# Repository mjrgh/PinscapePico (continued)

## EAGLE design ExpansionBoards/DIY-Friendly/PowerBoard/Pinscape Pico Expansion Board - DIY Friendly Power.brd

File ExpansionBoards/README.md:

# Pinscape Pico Expansion Boards

This folder has EAGLE plans for several circuit board designs that go with
the Pinscape Pico software.  These plans are all open-source designs that
anyone is free to build.

* <b>DIY-Friendly:</b> A comprehensive I/O controller for a virtual pinball
cabinet, with enough button ports and feedback device ports to connect just
about everything in a high-end build.  It uses entirely through-hole parts
that are easy to solder by hand, which is what makes it DIY-friendly.  The
project consists of two boards that are meant to be built and deployed as
a set (since I couldn't fit everything onto a single board, given the amount
of space that the through-hole parts take up).

* <b>Pro:</b> Another comprehensive expansion board, with essentially the
same functionality as the DIY-Friendly board set, but this time using mostly
surface-mount (SMD) parts.  The SMD parts are much smaller than the through-hole
parts used on the DIY board, allowing everything to be packed into a single
board.  The tradeoff is that a lot of the SMD parts used in the design are
difficult to solder by hand, precisely because they're so small.  So this
board is really meant to be assembled by factory equipment.  That's why I
refer to it as the "Pro" board - it's probably only going to be cost-effective
to build if you're going to build at least 50 or 100 units, and if you're
making that many, it's probably because you plan to sell them at a profit.
The designs are open-source, so you're free to do that if you have a retail
shop set up and you're willing to back your sales with warranty and technical
support (since, as they're open source, the designs themselves don't come
with any warranty).

* <b>IR-RX:</b> A small satellite board for the DIY-Friendly or Pro boards
that holds an IR receiver chip, and connects back to the expansion board
with a ribbon cable.  This lets you position an IR receiver anywhere
inside or outside your cabinet, so that it can be in line-of-sight to the
remote controls you want to point at it.

* <b>KL25Z Adapter:</b> This is for people with an existing set of the
original Pinscape KL25Z expansion boards.  The board plugs into the KL25Z
expansion boards where the KL25Z would normally go, letting a Pico take the
place of the KL25Z.  This lets you use your existing expansion boards with
the new Pinscape Pico software, and without having to re-wire your cabinet
for a new expansion board set.  (It doesn't act as a true general-purpose
KL25Z emulator, though, since it's very specifically wired for the original
Pinscape boards.)

* <b>Power Distribution:</b> A simple board designed to help tidy up your
virtual pin cab power supply wiring.  It doesn't do much other than route
power from one connector to another, but the idea is that it makes your
wiring simpler and more structured.  It does have a few active features: it
has a 6.3V regulator for powering #555 lamps (the type commonly used in
arcade pushbuttons); it provides main power switching (through a relay) for
all of the secondary supplies, based on the main PC power on/off status; and
it includes wiring for a coin door safety interlock switch for a
high-voltage (48V) supply, so that the high-voltage power is automatically
cut off whenever you open the coin door to do maintenance work inside the
cabinet.  It also features connectors that match the power connectors on the
DIY-Friendly and Pro expansion boards, again just to make the wiring tidier.
<p>
This board can be used with any I/O controller, not just Pinscape
Pico.  It does include two connectors designed especially to match
the layout of the Pinscape Pico expansion board power inputs, but
other controllers are likely to have similar power input requirements,
so it should be easy to adapt in most cases.
</p>

* <b>Flasher Panel:</b> A board designed to sit behind an RGB LED flasher
panel in a standard-width pin cab, to provide all of the electronics and
wiring to the flashers, including the five high-current (350mA) RGB LEDs.
It uses a 16-wire ribbon cable connector that matches the layout of the
Flasher port on the Pinscape Pico and KL25Z expansion boards, to make the
wiring between the controller and panel very easy and neat.  Like the Power
Distribution board, this one is designed to replace ad hoc wiring to make
your build a little tidier, and it can be used with any I/O controller.

## How to fabricate the boards

See [Fabricating the Expansion Boards](http://mjrnet.org/pinscape/BuildGuideV2/BuildGuide.php?sid=expanFab)
in the [Pinscape Build Guide](http://mjrnet.org/pinscape/BuildGuideV2/BuildGuide.php).
That explains the process in terms of the original KL25Z Pinscape boards, but
it applies equally well to the Pinscape Pico boards - just substitute the EAGLE
files from this repository.

## Bills of Materials (BOMs)

Each circuit board has an accompanying BOM file, in .csv (Comma-Separated
Value) format.  To view these, open them in a spreadsheet program like
Microsoft Excel, Apple Numbers, or Google Sheets.

The reason these are in CSV format rather than plain text is that Mouser and
Digikey will accept them as uploads, to construct a shopping cart without a
lot of manual data entry.  But you should carefully review the results.  For
one thing, the sites aren't always perfect at matching the BOM line items to
their inventory, so check that everything looks plausibly correct before
ordering.  For another, items go out of stock.  Some items might even be out
of production by the time you order, especially if the BOM you're working
from is more than five minutes old, since the manufacturers constantly
change their product lineups.  For out-of-stock or obsolete items, you'll
have to select suitable substitutes.  For generic parts like resistors and
capacitors, substitutes should always be easy to find - just match the Ohms
or "uF" values, and the physical package type and size.  For more complex
parts, such as transistors and IC chips, it can be more difficult to select
substitutes; ask on the forums if you're in doubt, and hopefully someone
with an electronics background can point you in the right direction.

## Copyright and license

The expansion board material is released under the same copyright and
license terms as the rest of the Pinscape Pico project.  Copyright 2025
Michael J Roberts; released under a BSD 3-clause license with NO WARRANTY.

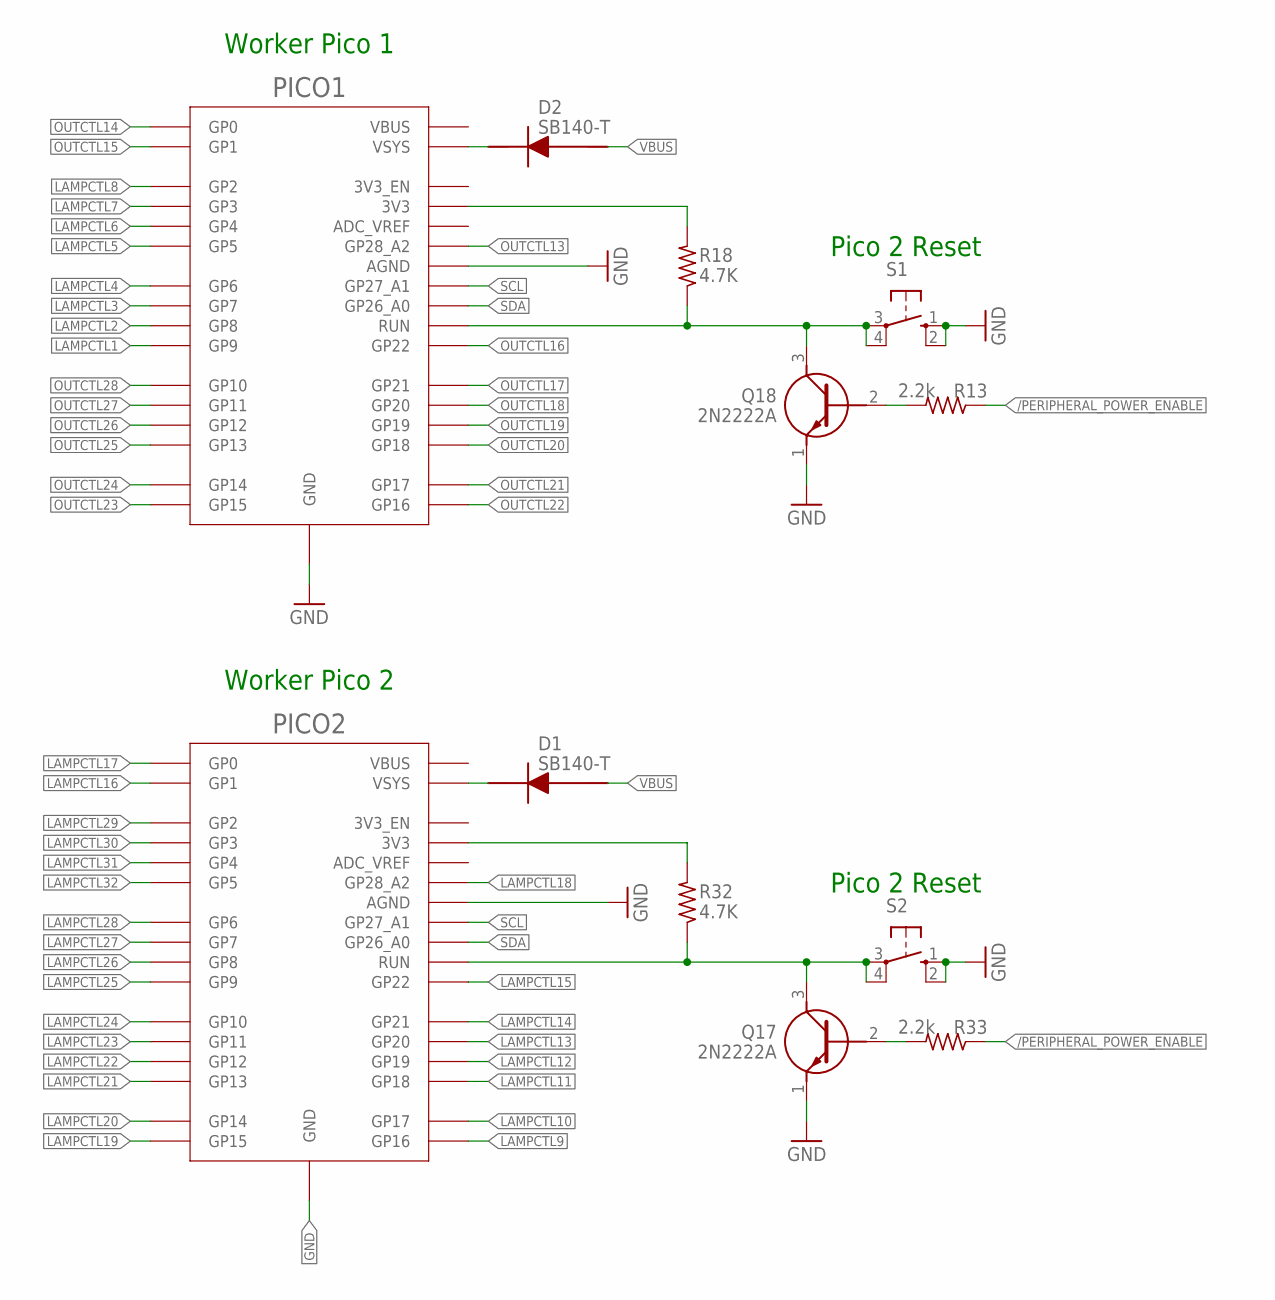
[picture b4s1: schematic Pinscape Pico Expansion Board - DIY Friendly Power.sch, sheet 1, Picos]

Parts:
D1, D2: SB140-T; DIOAD1408W86L464D236
PICO1, PICO2: RPI_PICO_NO_DEBUG; RPI_PICO_TH_NO_DEBUG
Q17, Q18: 2N2222A
R13, R33: 2.2k; 0204/7; PARTNO 660-MFS1/4DCT52R47R0
R18, R32: 4.7K; 0204/7; PARTNO 660-MFS1/4DCT52R47R0
S1, S2: 10-XX; B3F-10XX

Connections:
/PERIPHERAL_POWER_ENABLE: R13.1, R33.1; also elsewhere on the board
GND: PICO1.AGND, PICO1.GND@1 (GND), PICO1.GND@2 (GND), PICO1.GND@3 (GND), PICO1.GND@4 (GND), PICO1.GND@6 (GND), PICO1.GND@7 (GND), PICO1.GND@8 (GND), PICO2.AGND, PICO2.GND@1 (GND), PICO2.GND@2 (GND), PICO2.GND@3 (GND), PICO2.GND@4 (GND), PICO2.GND@6 (GND), PICO2.GND@7 (GND), PICO2.GND@8 (GND), Q17.1 (E), Q18.1 (E), S1.1 (S), S1.2 (S1), S2.1 (S), S2.2 (S1); also elsewhere on the board
LAMPCTL1: PICO1.GP9; also elsewhere on the board
LAMPCTL2: PICO1.GP8; also elsewhere on the board
LAMPCTL3: PICO1.GP7; also elsewhere on the board
LAMPCTL4: PICO1.GP6; also elsewhere on the board
LAMPCTL5: PICO1.GP5; also elsewhere on the board
LAMPCTL6: PICO1.GP4; also elsewhere on the board
LAMPCTL7: PICO1.GP3; also elsewhere on the board
LAMPCTL8: PICO1.GP2; also elsewhere on the board
LAMPCTL9: PICO2.GP16; also elsewhere on the board
LAMPCTL10: PICO2.GP17; also elsewhere on the board
LAMPCTL11: PICO2.GP18; also elsewhere on the board
LAMPCTL12: PICO2.GP19; also elsewhere on the board
LAMPCTL13: PICO2.GP20; also elsewhere on the board
LAMPCTL14: PICO2.GP21; also elsewhere on the board
LAMPCTL15: PICO2.GP22; also elsewhere on the board
LAMPCTL16: PICO2.GP1; also elsewhere on the board
LAMPCTL17: PICO2.GP0; also elsewhere on the board
LAMPCTL18: PICO2.GP28_A2; also elsewhere on the board
LAMPCTL19: PICO2.GP15; also elsewhere on the board
LAMPCTL20: PICO2.GP14; also elsewhere on the board
LAMPCTL21: PICO2.GP13; also elsewhere on the board
LAMPCTL22: PICO2.GP12; also elsewhere on the board
LAMPCTL23: PICO2.GP11; also elsewhere on the board
LAMPCTL24: PICO2.GP10; also elsewhere on the board
LAMPCTL25: PICO2.GP9; also elsewhere on the board
LAMPCTL26: PICO2.GP8; also elsewhere on the board
LAMPCTL27: PICO2.GP7; also elsewhere on the board
LAMPCTL28: PICO2.GP6; also elsewhere on the board
LAMPCTL29: PICO2.GP2; also elsewhere on the board
LAMPCTL30: PICO2.GP3; also elsewhere on the board
LAMPCTL31: PICO2.GP4; also elsewhere on the board
LAMPCTL32: PICO2.GP5; also elsewhere on the board
unnamed: D1.1 (K), PICO2.VSYS
unnamed: D2.1 (K), PICO1.VSYS
unnamed: PICO2.3V3, R32.2
unnamed: Q17.2 (B), R33.2
unnamed: PICO2.RUN, Q17.3 (C), R32.1, S2.3, S2.4 (P1)
unnamed: PICO1.3V3, R18.2
unnamed: Q18.2 (B), R13.2
unnamed: PICO1.RUN, Q18.3 (C), R18.1, S1.3, S1.4 (P1)
OUTCTL13: PICO1.GP28_A2; also elsewhere on the board
OUTCTL14: PICO1.GP0; also elsewhere on the board
OUTCTL15: PICO1.GP1; also elsewhere on the board
OUTCTL16: PICO1.GP22; also elsewhere on the board
OUTCTL17: PICO1.GP21; also elsewhere on the board
OUTCTL18: PICO1.GP20; also elsewhere on the board
OUTCTL19: PICO1.GP19; also elsewhere on the board
OUTCTL20: PICO1.GP18; also elsewhere on the board
OUTCTL21: PICO1.GP17; also elsewhere on the board
OUTCTL22: PICO1.GP16; also elsewhere on the board
OUTCTL23: PICO1.GP15; also elsewhere on the board
OUTCTL24: PICO1.GP14; also elsewhere on the board
OUTCTL25: PICO1.GP13; also elsewhere on the board
OUTCTL26: PICO1.GP12; also elsewhere on the board
OUTCTL27: PICO1.GP11; also elsewhere on the board
OUTCTL28: PICO1.GP10; also elsewhere on the board
SCL: PICO1.GP27_A1, PICO2.GP27_A1; also elsewhere on the board
SDA: PICO1.GP26_A0, PICO2.GP26_A0; also elsewhere on the board
VBUS: D1.2 (A), D2.2 (A); also elsewhere on the board

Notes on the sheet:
Worker Pico 1
Worker Pico 2
Pico 2 Reset

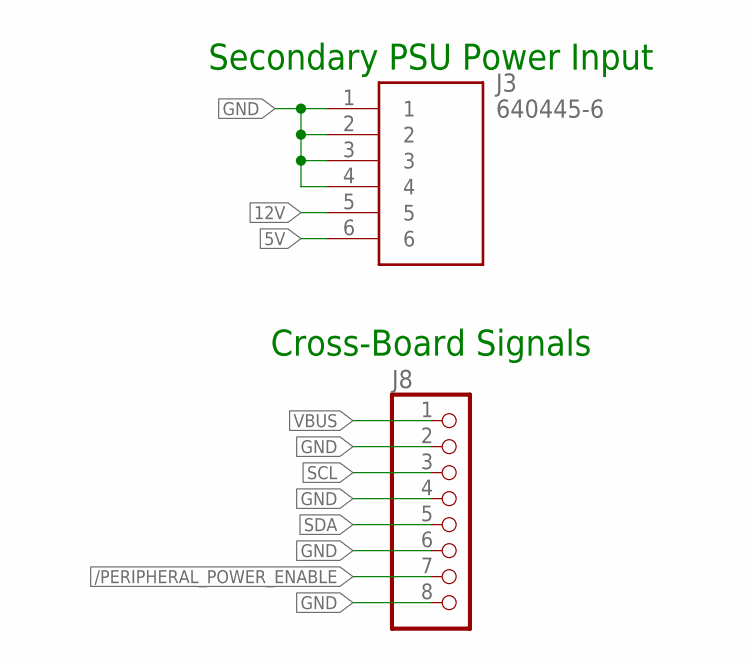
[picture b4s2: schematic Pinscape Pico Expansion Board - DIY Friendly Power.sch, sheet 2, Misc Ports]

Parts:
J3: 640445-6; SHDR6W183P0X396_1X6_2377X762X1
J8: PINHD-1X8/90; 1X08/90

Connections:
5V: J3.6; also elsewhere on the board
12V: J3.5; also elsewhere on the board
/PERIPHERAL_POWER_ENABLE: J8.7; also elsewhere on the board
GND: J3.1, J3.2, J3.3, J3.4, J8.2, J8.4, J8.6, J8.8; also elsewhere on the board
SCL: J8.3; also elsewhere on the board
SDA: J8.5; also elsewhere on the board
VBUS: J8.1; also elsewhere on the board

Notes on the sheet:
Secondary PSU Power Input
Cross-Board Signals

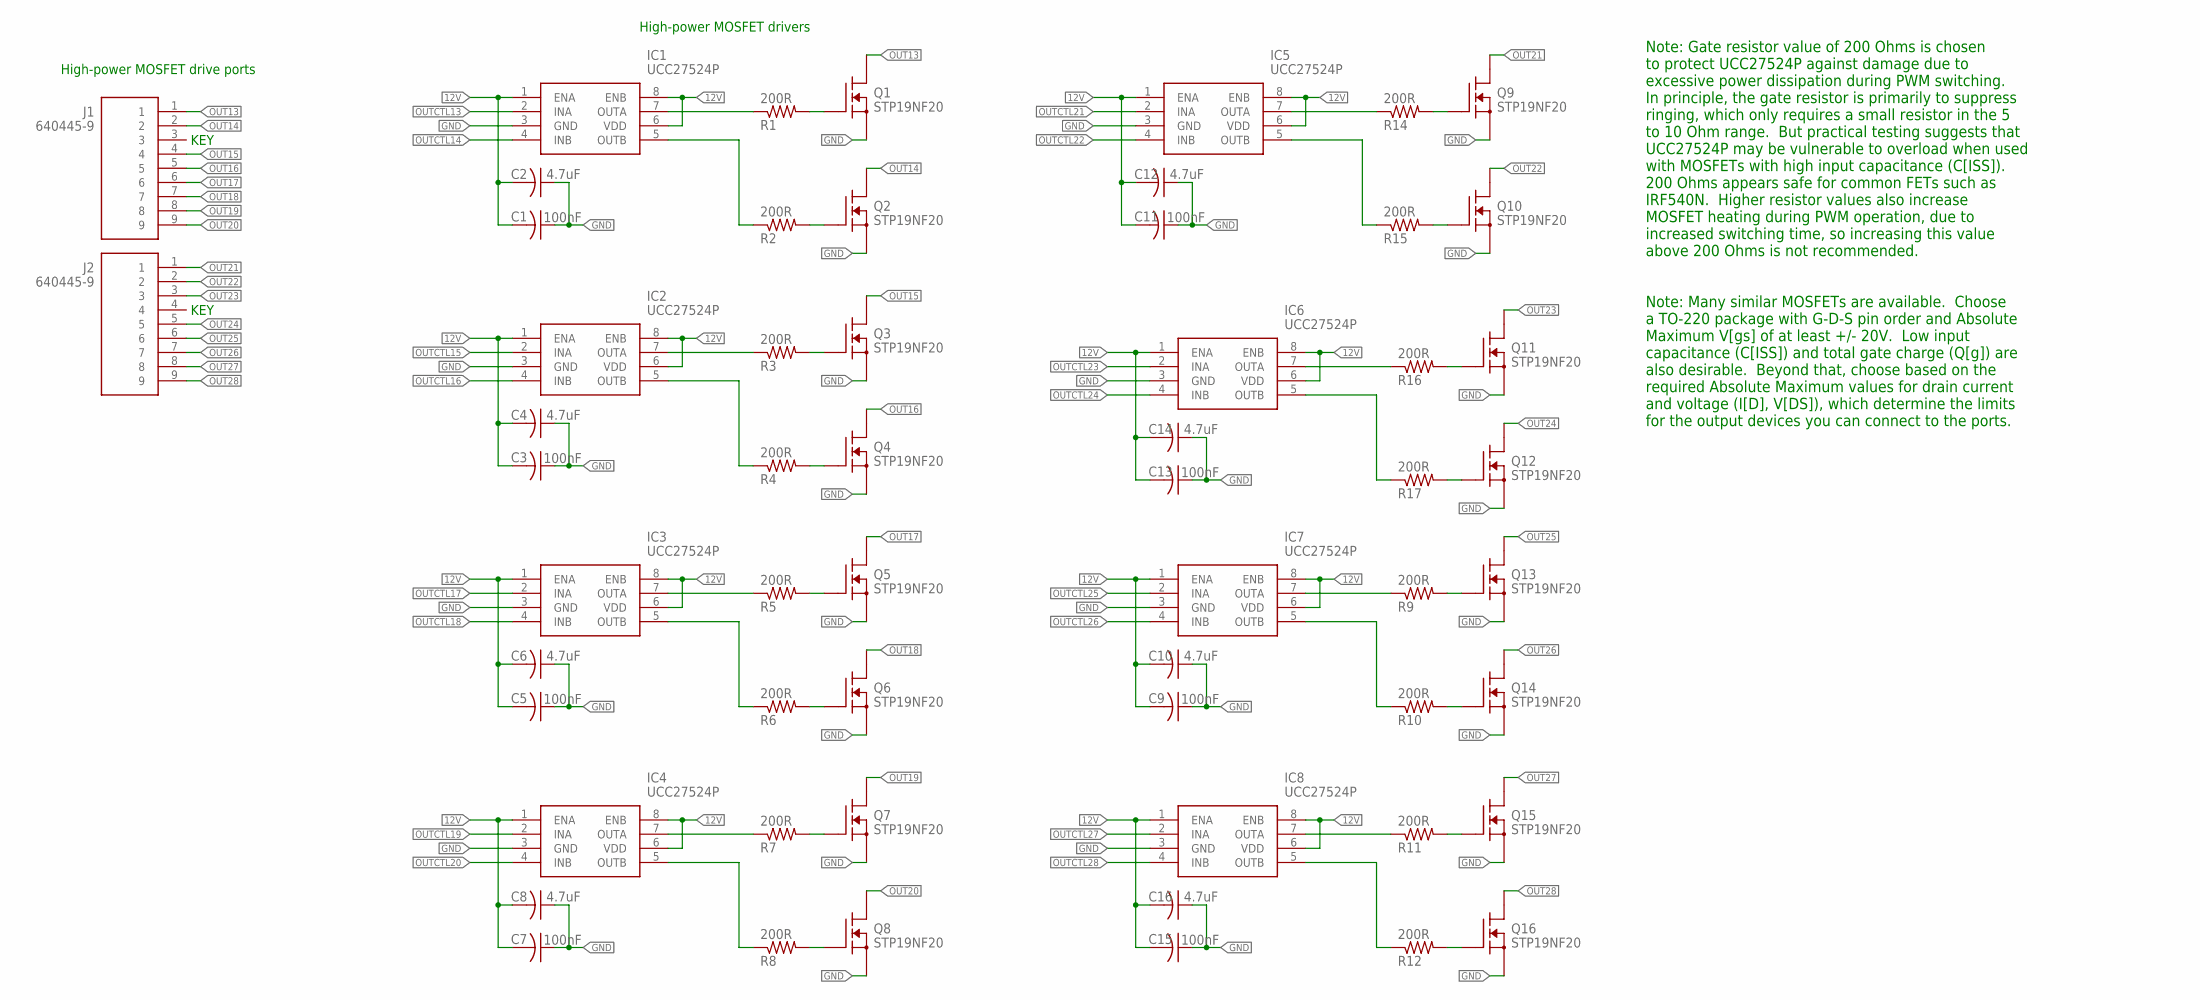
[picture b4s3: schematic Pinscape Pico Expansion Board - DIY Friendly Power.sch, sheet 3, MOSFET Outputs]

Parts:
C1, C3, C5, C7, C9, C11, C13, C15: 100nF; C025-024X044; PARTNO 21RZ310-RC
C2, C4, C6, C8, C10, C12, C14, C16: 4.7uF; C025-024X044; PARTNO 810-FG14X5R1H475KRT0
IC1, IC2, IC3, IC4, IC5, IC6, IC7, IC8: UCC27524P; DIP794W53P254L959H508Q8N
J1, J2: 640445-9; SHDR9W117P0X396_1X9_3566X762X1
Q1, Q2, Q3, Q4, Q5, Q6, Q7, Q8, Q9, Q10, Q11, Q12, Q13, Q14, Q15, Q16: STP19NF20; TO220BV; PARTNO FDPF085N10A
R1, R2, R3, R4, R5, R6, R7, R8, R9, R10, R11, R12, R14, R15, R16, R17: 200R; 0204/5; PARTNO 660-MFS1/4DCT52R47R0

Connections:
12V: C1.2, C2.2, C3.2, C4.2, C5.2, C6.2, C7.2, C8.2, C9.2, C10.2, C11.2, C12.2, C13.2, C14.2, C15.2, C16.2, IC1.1 (ENA), IC1.6 (VDD), IC1.8 (ENB), IC2.1 (ENA), IC2.6 (VDD), IC2.8 (ENB), IC3.1 (ENA), IC3.6 (VDD), IC3.8 (ENB), IC4.1 (ENA), IC4.6 (VDD), IC4.8 (ENB), IC5.1 (ENA), IC5.6 (VDD), IC5.8 (ENB), IC6.1 (ENA), IC6.6 (VDD), IC6.8 (ENB), IC7.1 (ENA), IC7.6 (VDD), IC7.8 (ENB), IC8.1 (ENA), IC8.6 (VDD), IC8.8 (ENB); also elsewhere on the board
GND: C1.1, C2.1, C3.1, C4.1, C5.1, C6.1, C7.1, C8.1, C9.1, C10.1, C11.1, C12.1, C13.1, C14.1, C15.1, C16.1, IC1.3 (GND), IC2.3 (GND), IC3.3 (GND), IC4.3 (GND), IC5.3 (GND), IC6.3 (GND), IC7.3 (GND), IC8.3 (GND), Q1.3 (S), Q2.3 (S), Q3.3 (S), Q4.3 (S), Q5.3 (S), Q6.3 (S), Q7.3 (S), Q8.3 (S), Q9.3 (S), Q10.3 (S), Q11.3 (S), Q12.3 (S), Q13.3 (S), Q14.3 (S), Q15.3 (S), Q16.3 (S); also elsewhere on the board
unnamed: IC1.7 (OUTA), R1.1
unnamed: IC1.5 (OUTB), R2.1
unnamed: Q1.1 (G), R1.2
unnamed: Q2.1 (G), R2.2
unnamed: IC2.7 (OUTA), R3.1
unnamed: IC2.5 (OUTB), R4.1
unnamed: Q3.1 (G), R3.2
unnamed: Q4.1 (G), R4.2
unnamed: IC3.7 (OUTA), R5.1
unnamed: IC3.5 (OUTB), R6.1
unnamed: Q5.1 (G), R5.2
unnamed: Q6.1 (G), R6.2
unnamed: IC4.7 (OUTA), R7.1
unnamed: IC4.5 (OUTB), R8.1
unnamed: Q7.1 (G), R7.2
unnamed: Q8.1 (G), R8.2
unnamed: IC5.7 (OUTA), R14.1
unnamed: IC5.5 (OUTB), R15.1
unnamed: IC7.7 (OUTA), R9.1
unnamed: IC7.5 (OUTB), R10.1
unnamed: Q13.1 (G), R9.2
unnamed: Q14.1 (G), R10.2
unnamed: Q9.1 (G), R14.2
unnamed: Q10.1 (G), R15.2
unnamed: IC6.7 (OUTA), R16.1
unnamed: IC6.5 (OUTB), R17.1
unnamed: Q11.1 (G), R16.2
unnamed: Q12.1 (G), R17.2
unnamed: IC8.7 (OUTA), R11.1
unnamed: IC8.5 (OUTB), R12.1
unnamed: Q15.1 (G), R11.2
unnamed: Q16.1 (G), R12.2
OUT13: J1.1, Q1.2 (D)
OUT14: J1.2, Q2.2 (D)
OUT15: J1.4, Q3.2 (D)
OUT16: J1.5, Q4.2 (D)
OUT17: J1.6, Q5.2 (D)
OUT18: J1.7, Q6.2 (D)
OUT19: J1.8, Q7.2 (D)
OUT20: J1.9, Q8.2 (D)
OUT21: J2.1, Q9.2 (D)
OUT22: J2.2, Q10.2 (D)
OUT23: J2.3, Q11.2 (D)
OUT24: J2.5, Q12.2 (D)
OUT25: J2.6, Q13.2 (D)
OUT26: J2.7, Q14.2 (D)
OUT27: J2.8, Q15.2 (D)
OUT28: J2.9, Q16.2 (D)
OUTCTL13: IC1.2 (INA); also elsewhere on the board
OUTCTL14: IC1.4 (INB); also elsewhere on the board
OUTCTL15: IC2.2 (INA); also elsewhere on the board
OUTCTL16: IC2.4 (INB); also elsewhere on the board
OUTCTL17: IC3.2 (INA); also elsewhere on the board
OUTCTL18: IC3.4 (INB); also elsewhere on the board
OUTCTL19: IC4.2 (INA); also elsewhere on the board
OUTCTL20: IC4.4 (INB); also elsewhere on the board
OUTCTL21: IC5.2 (INA); also elsewhere on the board
OUTCTL22: IC5.4 (INB); also elsewhere on the board
OUTCTL23: IC6.2 (INA); also elsewhere on the board
OUTCTL24: IC6.4 (INB); also elsewhere on the board
OUTCTL25: IC7.2 (INA); also elsewhere on the board
OUTCTL26: IC7.4 (INB); also elsewhere on the board
OUTCTL27: IC8.2 (INA); also elsewhere on the board
OUTCTL28: IC8.4 (INB); also elsewhere on the board

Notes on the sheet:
High-power MOSFET drive ports
KEY
High-power MOSFET drivers
Note: Gate resistor value of 200 Ohms is chosen to protect UCC27524P against damage due to excessive power dissipation during PWM switching. In principle, the gate resistor is primarily to suppress ringing, which only requires a small resistor in the 5 to 10 Ohm range. But practical testing suggest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
Note: Many similar MOSFETs are available. Choose a TO-220 package with G-D-S pin order and Absolute Maximum V[gs] of at least +/- 20V. Low input capacitance (C[ISS]) and total gate charge (Q[g]) are also desirable. Beyond that, choose based on the required Absolute Maximum values for drain current 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

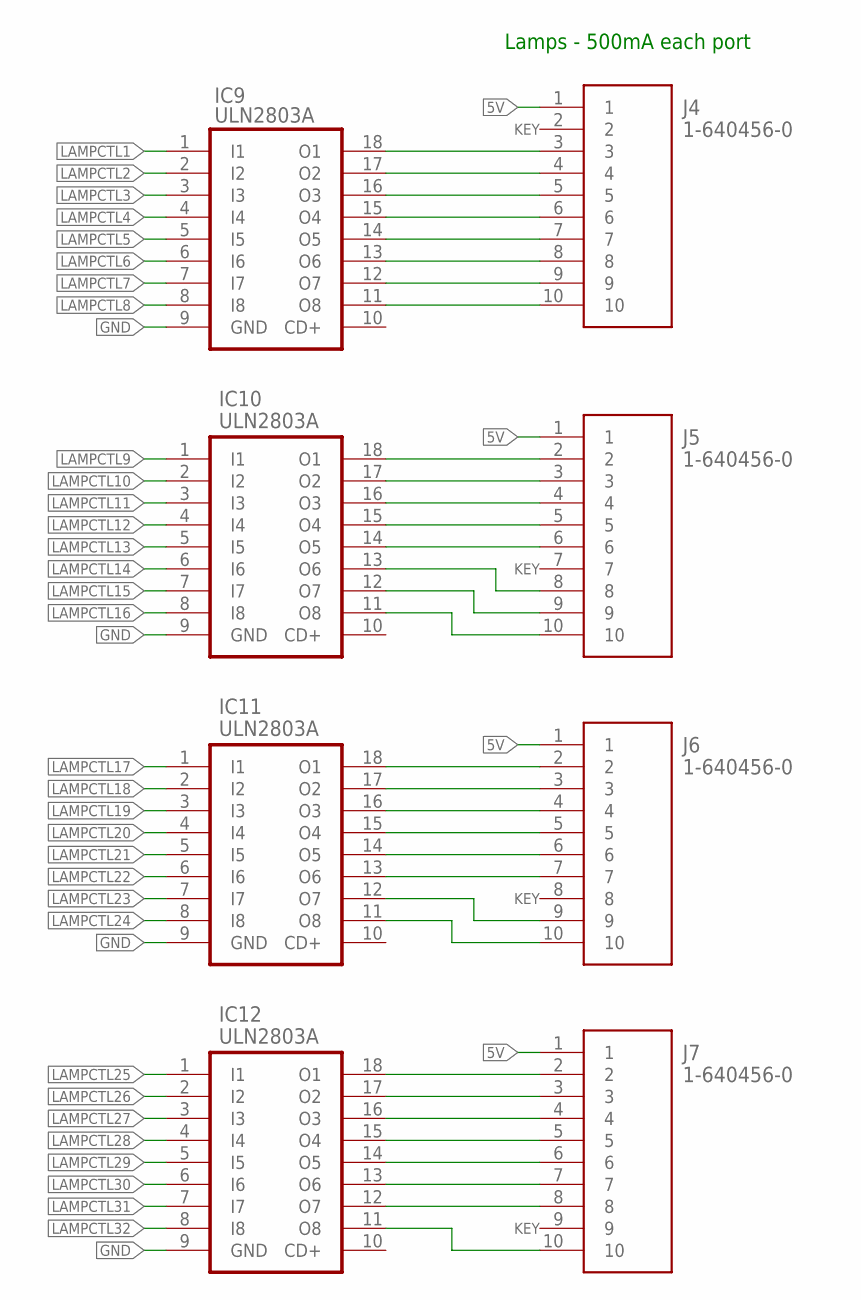
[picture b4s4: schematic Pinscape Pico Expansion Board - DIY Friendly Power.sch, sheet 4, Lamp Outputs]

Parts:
IC9, IC10, IC11, IC12: ULN2803A; DIL18
J4, J5, J6, J7: 1-640456-0; SHDR10W66P0X254_1X10_2540X572X

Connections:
5V: J4.1, J5.1, J6.1, J7.1; also elsewhere on the board
GND: IC9.9 (GND), IC10.9 (GND), IC11.9 (GND), IC12.9 (GND); also elsewhere on the board
LAMPCTL1: IC9.1 (I1); also elsewhere on the board
LAMPCTL2: IC9.2 (I2); also elsewhere on the board
LAMPCTL3: IC9.3 (I3); also elsewhere on the board
LAMPCTL4: IC9.4 (I4); also elsewhere on the board
LAMPCTL5: IC9.5 (I5); also elsewhere on the board
LAMPCTL6: IC9.6 (I6); also elsewhere on the board
LAMPCTL7: IC9.7 (I7); also elsewhere on the board
LAMPCTL8: IC9.8 (I8); also elsewhere on the board
LAMPCTL9: IC10.1 (I1); also elsewhere on the board
LAMPCTL10: IC10.2 (I2); also elsewhere on the board
LAMPCTL11: IC10.3 (I3); also elsewhere on the board
LAMPCTL12: IC10.4 (I4); also elsewhere on the board
LAMPCTL13: IC10.5 (I5); also elsewhere on the board
LAMPCTL14: IC10.6 (I6); also elsewhere on the board
LAMPCTL15: IC10.7 (I7); also elsewhere on the board
LAMPCTL16: IC10.8 (I8); also elsewhere on the board
LAMPCTL17: IC11.1 (I1); also elsewhere on the board
LAMPCTL18: IC11.2 (I2); also elsewhere on the board
LAMPCTL19: IC11.3 (I3); also elsewhere on the board
LAMPCTL20: IC11.4 (I4); also elsewhere on the board
LAMPCTL21: IC11.5 (I5); also elsewhere on the board
LAMPCTL22: IC11.6 (I6); also elsewhere on the board
LAMPCTL23: IC11.7 (I7); also elsewhere on the board
LAMPCTL24: IC11.8 (I8); also elsewhere on the board
LAMPCTL25: IC12.1 (I1); also elsewhere on the board
LAMPCTL26: IC12.2 (I2); also elsewhere on the board
LAMPCTL27: IC12.3 (I3); also elsewhere on the board
LAMPCTL28: IC12.4 (I4); also elsewhere on the board
LAMPCTL29: IC12.5 (I5); also elsewhere on the board
LAMPCTL30: IC12.6 (I6); also elsewhere on the board
LAMPCTL31: IC12.7 (I7); also elsewhere on the board
LAMPCTL32: IC12.8 (I8); also elsewhere on the board
unnamed: IC12.18 (O1), J7.2
unnamed: IC12.17 (O2), J7.3
unnamed: IC12.16 (O3), J7.4
unnamed: IC12.15 (O4), J7.5
unnamed: IC12.14 (O5), J7.6
unnamed: IC12.13 (O6), J7.7
unnamed: IC12.12 (O7), J7.8
unnamed: IC12.11 (O8), J7.10
unnamed: IC11.18 (O1), J6.2
unnamed: IC11.17 (O2), J6.3
unnamed: IC11.16 (O3), J6.4
unnamed: IC11.15 (O4), J6.5
unnamed: IC11.14 (O5), J6.6
unnamed: IC11.13 (O6), J6.7
unnamed: IC11.12 (O7), J6.9
unnamed: IC11.11 (O8), J6.10
unnamed: IC9.18 (O1), J4.3
unnamed: IC9.17 (O2), J4.4
unnamed: IC9.16 (O3), J4.5
unnamed: IC9.15 (O4), J4.6
unnamed: IC9.14 (O5), J4.7
unnamed: IC9.13 (O6), J4.8
unnamed: IC9.12 (O7), J4.9
unnamed: IC9.11 (O8), J4.10
unnamed: IC10.18 (O1), J5.2
unnamed: IC10.17 (O2), J5.3
unnamed: IC10.16 (O3), J5.4
unnamed: IC10.15 (O4), J5.5
unnamed: IC10.14 (O5), J5.6
unnamed: IC10.13 (O6), J5.8
unnamed: IC10.12 (O7), J5.9
unnamed: IC10.11 (O8), J5.10

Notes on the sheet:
Lamps - 500mA each port
KEY

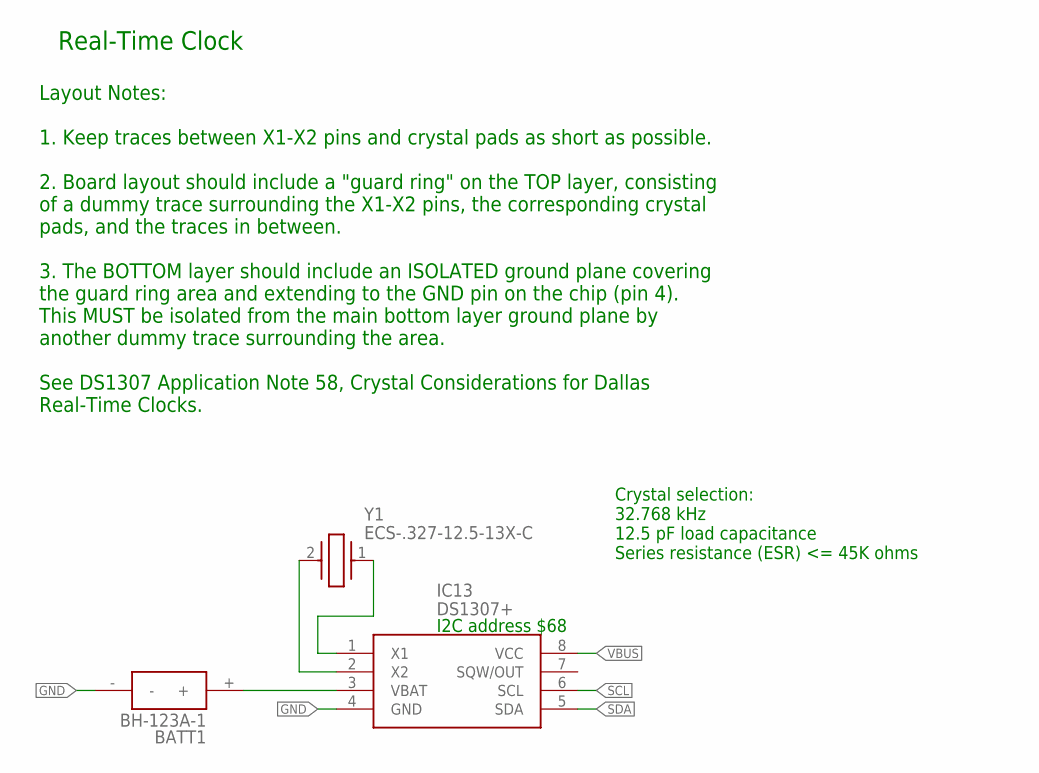
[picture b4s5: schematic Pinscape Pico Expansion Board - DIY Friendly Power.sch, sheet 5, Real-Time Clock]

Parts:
BATT1: BH-123A-1
IC13: DS1307+; DIP794W56P254L938H457Q8N
Y1: ECS-.327-12.5-13X-C; ECS32712513XC

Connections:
GND: BATT1.-, IC13.4 (GND); also elsewhere on the board
unnamed: BATT1.+, IC13.3 (VBAT)
unnamed: IC13.1 (X1), Y1.1 (CRYSTAL_1)
unnamed: IC13.2 (X2), Y1.2 (CRYSTAL_2)
SCL: IC13.6 (SCL); also elsewhere on the board
SDA: IC13.5 (SDA); also elsewhere on the board
VBUS: IC13.8 (VCC); also elsewhere on the board

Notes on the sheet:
Real-Time Clock
Crystal selection: 32.768 kHz 12.5 pF load capacitance Series resistance (ESR) <= 45K ohms
I2C address $68
Layout Notes: 1. Keep traces between X1-X2 pins and crystal pads as short as possible. 2. Board layout should include a "guard ring" on the TOP layer, consisting of a dummy trace surrounding the X1-X2 pins, the corresponding crystal pads, and the traces in between. 3. The BOTTOM layer should includ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

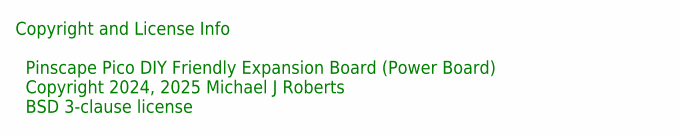
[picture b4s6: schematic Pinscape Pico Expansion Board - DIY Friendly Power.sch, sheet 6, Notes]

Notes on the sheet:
Copyright and License Info Pinscape Pico DIY Friendly Expansion Board (Power Board) Copyright 2024, 2025 Michael J Roberts BSD 3-clause license

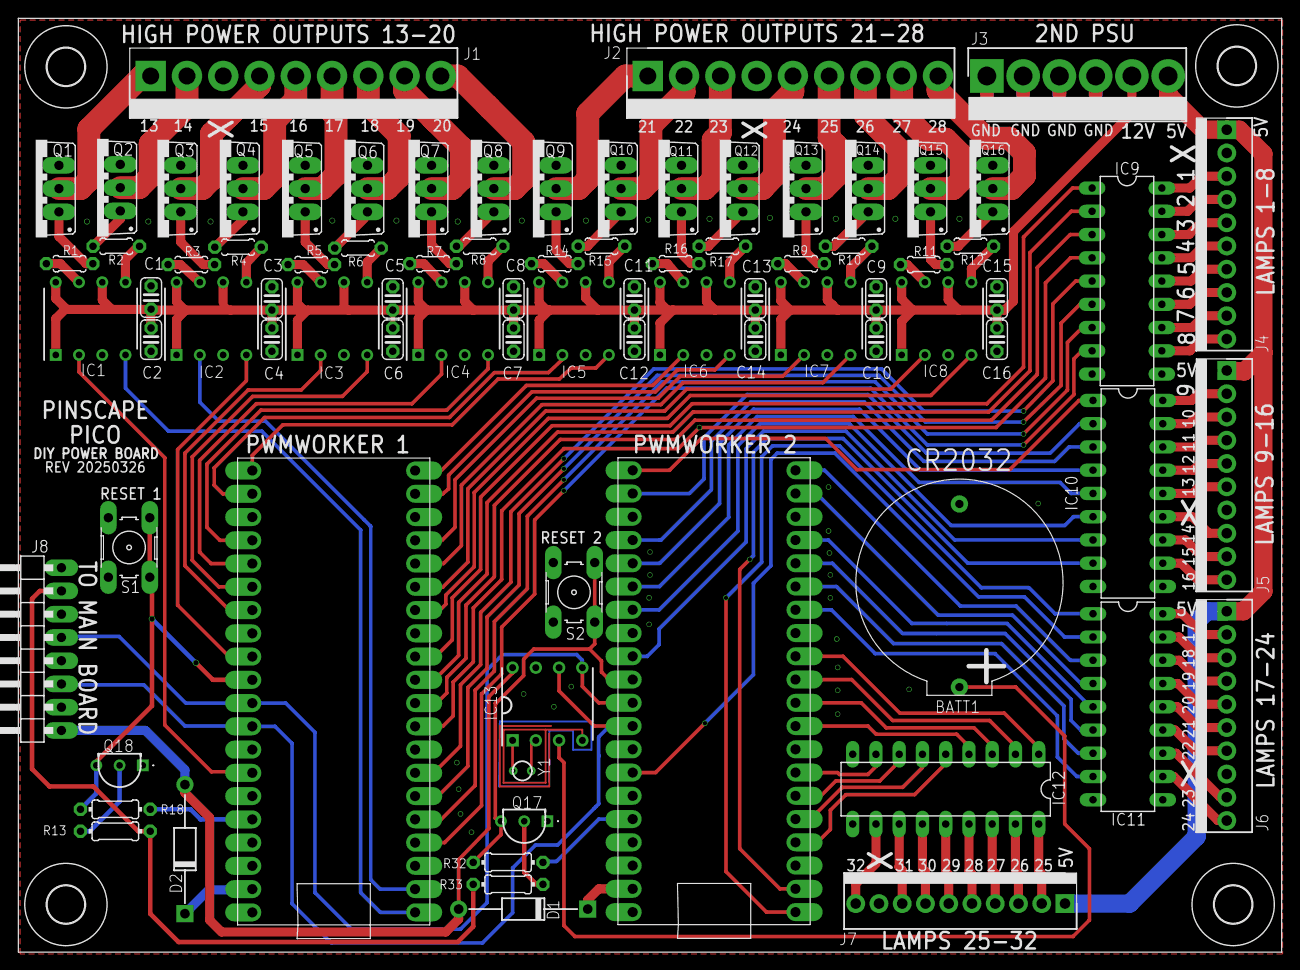
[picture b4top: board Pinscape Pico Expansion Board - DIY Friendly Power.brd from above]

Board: 2 copper layers, 138.0 x 102.0 mm, 87 parts (0 on the bottom side), 146 nets.

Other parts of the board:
U$1, U$2, U$3, U$4: 4,1

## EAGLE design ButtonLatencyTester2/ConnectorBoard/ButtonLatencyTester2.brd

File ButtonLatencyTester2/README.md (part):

# Button Latency Tester II

This is a Pinscape Pico sub-project that turns a Raspberry Pi Pico into
a piece of test equipment for measuring button input latency on **another**
device.  The other device, which we'll refer to as the "subject" device
because it's the subject of the measurements, can be **any type of device**,
Pico or otherwise, that takes physical button inputs and turns them into
some kind of input to a Windows PC.  The subject device could be:

* Another Pico running the Pico Pinscape firmware

* Another Pico running some <i>non-</i>Pinscape firmware, such as Dude's Cab Controller or RickH's Little Bang controller

* A KL25Z running the original Pinscape firmware

* A proprietary key encoder, such as an Ultimarc I-PAC or a Zero Delay encoder

* A USB or PS/2-port keyboard

* A serial-port joystick

The last two (a physical keyboard or joystick) are less practical than
the others, because the testing setup requires physical access to the
switch wiring in the subject device, thus you'd have to do some
invasive surgery if you wanted to test a real keyboard or joystick.
It's much easier to work with button encoder devices that are designed
from the ground up to be connected to external button switches.  But I
wanted to make the point that you *could*, at least in principle, use
BLT-II to measure just about anything with buttons that sends input to
a PC.

This project is nominally part of Pinscape Pico, but you can also use
it as a standalone measurement tool for other types of devices.  You
don't need to install the main Pinscape firmware onto any devices to
use it.  You only need to install the much simpler Button Latency
Tester II firmware, which doesn't require any configuration.

## API selection

The Windows host program can read input through four different Windows
APIs:

* Raw Input

* DirectInput 8

* XInput (Microsoft's special API for XBox controller devices)

* [Open Pinball Device](http://mjrnet.org/pinscape/OpenPinballDevice/OpenPinballDeviceHID.htm)

When you map a physical button on the subject device to XInput or Open
Pinball Device buttons, the host program automatically uses those
respective APIs, because they go hand-in-hand with the sources.

For keyboard and gamepad button inputs, you get your pick of Raw Input or
DirectInput.  Raw Input is the default, because it's much faster than
DirectInput, and also because it's the "modern" API that Microsoft
recommends.  Microsoft deprecated DirectInput many years ago (way back in
the Windows 7 timeframe), because Microsoft likes to invent new APIs every
few years that do exactly the same thing as the old APIs they replace.  But
in this case, they had the right idea, because DirectInput is objectively
horrible, as you will see when you run tests with this program.  DirectInput's
median latency for joystick and keyboard events is about 5x greater than Raw
Input's when reading exactly the same devices, and at its worst, DirectInput
reaches the human-perceptible latency range of around 30ms.

To select DirectInput, add `--api directinput` to the command line when
running the host program.

### Initial findings about the APIs

My own ad hoc testing indicates that applications should use Raw Input
and Open Pinball Device whenever possible.  With Pinscape Pico devices
(which are designed to yield the minimum possible HID-level latency),
Raw Input and Open Pinball Device provide a median latency slightly under 2ms,
with excellent consistency (standard deviation in the 0.3ms range, and
maximum latencies around 3ms).  That's nearly as fast as HID can deliver
input directly at the hardware level, which means that Raw Input is adding
practically no overhead of its own, as Microsoft claims.

DirectInput 8 is by far the worst API, with median latency around 9ms,
and extremely wide variation, up to 30ms latency for some inputs.
Much to my surprise, XInput is almost as bad as DirectInput, with
median latency around 8ms and maximum latency around 25ms.  I would
have expected XInput to use the same low-level approach as Raw Input,
given that XInput is all about gaming, but empirically this doesn't
seem to be the case.

All of my testing was on Windows 11, so it's quite possible that the
numbers will vary somewhat on other versions, although I expect that
the hierarchy will be the same everywhere.  Note that my API
comparisons are very apples-to-apples, since they used the same
physical source for all of the input types, just with different
logical mappings for the buttons.

## Firmware installation

Install the Button Latency Tester II firmware using the standard Pico
boot loader procedure:

* Unplug the Pico from USB and all power sources

* Press **and hold** the BOOTSEL button (the small white button on top of
the Pico, labeled BOOTSEL)

* While still holding BOOTSEL, plug in the USB cable

* Release the BOOTSEL button

* The Pico should now appear on the Windows desktop as a virtual
USB thumb drive

* Copy ButtonLatencyTester2.uf2 onto the virtual thumb drive
representing the Pico

* The Pico will automatically reboot and start running the firmware

* From a Windows command prompt, run `ButtonLatencyTester2 --list` to
verify that the device appears in the list of recognized devices

* No configuration is required on the device side, and no device
drivers are required on the Windows side

## Companion Circuit Board

The project includes a [circuit board design](ConnectorBoard) that
implements the test bench setup described below on a small board that
you can plug a Pico into.  The circuit board includes inputs for four
buttons, and uses screw terminals for all external connections, to
make it easy to temporarily patch into an existing pin cab's button
encoder wiring.  The circuitry needed is also easy to set up on a
breadboard, so the PCB isn't a must.  But it might be worthwhile to
build if you plan to use it for more than one or two ad hoc test runs.

## Recommended Test Bench Setup - description

A crucial step in accurately measuring button latency is to capture
the exact moment when you press the button.  The whole point of the
exercise is to measure the time between the button press and the
arrival of the corresponding input event on the PC, so we need to know
the time of each of those endpoints, as precisely as possible.

To measure the time of the button press, we set up the button so that
it's physically connected to **both** the subject device and the
BLT-II Pico.  This ensures that the BLT-II Pico sees the physical
button press at exactly the same time as the subject device, giving us
an accurate reading on the beginning endpoint of the time interval
we're trying to measure.

The best way to connect a single button to both devices without any
risk of electrical interference between the two devices is to use an
optocoupler to isolate the button from each device.  In the
reference setup, the button is wired to **two** optocouplers: one
for the subject device, one for the BLT-II Pico.  When you press the
button, it activates both optocouplers simultaneously.  This sends the
button press signal to the subject device and the BLT-II Pico at the
same moment.  The subject device uses the input to initiate its input
event to the host, and the BLT-II Pico uses the signal to record the
time of the physical button press.

An optocoupler's transistor (Collector/Emitter) side acts roughly like
an ordinary switch, so in most encoder setups, it can physically take
the place of an ordinary pushbutton switch in a button input port's
wiring.  This works as long as the subject device's button input ports
are voltage-sensitive and high-impedance (very low current).  This is
true of the Pico, and also holds for most other microcontrollers.

## Recommended Test Bench Setup - how to

You'll need the following parts:

* A Raspberry Pi Pico, with the Button Latency Tester II firmware installed
(see above)

* The Subject Device (the device whose button latency you wish to measure),
with its firmware installed and configured for the scenario you wish to test

* A Windows PC, with the ButtonLatencyTester2.exe host program installed

* Two (2) PC817 optocouplers, or any equivalent optocouplers

* One 130 Ohm resistor

* One pushbutton

<b>IMPORTANT:</b> The diagram below assumes that the subject device uses **active-low**
button inputs.  This means that the subject device registers the button as ON when the
button terminal is connected to GND (ground), and registers the button as OFF when
the terminal is left floating (not connected to anything external).  For an active-low
controller, the **normal** wiring plan you'd use, in the absence of the test setup, is
as follows:

* Connect one terminal of the button to a button port on the subject device

* Connect the other terminal of the button to GND (ground)

If the subject device **doesn't** follow this wiring plan, you'll have to adjust
the test setup accordingly.  In *most* cases, the PC817 optocoupler in the test setup
simply takes the place of the button switch in the subject device's normal wiring
plan, but this isn't always possible.  This works as long as the device's button
input ports are voltage-sensitive and high-impedance (low current), which is true
for most microcontrollers.  If your subject device doesn't use active-low wiring, or
you're not sure that an optocoupler is a valid substitution for a physical switch for
its button wiring, check with the device's manufacturer or designer.  (Please also
let me know about it, so that I can list the specific cases people have come across
that don't fit the basic "active low" pattern.)

<b>REGARDLESS</b> of the subject device's wiring configuration, the BLT-II Pico portion
is **always** connected as shown in the diagram.  That's another reason to use the
optocoupler isolation setup: it makes the Pico wiring a constant, no matter how
the subject device is wired.

Wire the devices as shown in the diagram:

* Connect the first optocoupler pin 1 (LED +) to the Pico's VBUS port

* Connect the first optocoupler's pin2 (LED -) to the second optocoupler's pin1 (LED +)

* Connect the second optocoupler's pin2 (LED -) to the common ("C") terminal of the pushbutton switch

* Connect the Normally Open ("NO") terminal of the pushbutton to the 130 Ohm resistor

* Connect the other end of the resistor to any available GND (Ground) port on the Pico

* Connect the first optocoupler's pins 3 and 4 (Collector and Emitter) to the
button input GPIO port and GND terminals, respectively, on the Subject Device

* Connect the second optocoupler's pins 3 and 4 to GP0 and GND on the BLT-II Pico

You can test multiple buttons by wiring them just like the first
button, choosing a new GPIO port on the BLT-II Pico for each
additional button.  You'll need another full set of components (two
optocouplers and a resistor) for each additional button.  All 26 of
the Pico's GPIO ports are available as button inputs.  Note that you
can connect any GPIO set of ports you wish - there's no need to start
at GP0.  Our choice of GP0 as the first port in the diagram is
arbitrary.

## Run the program

Once your test bench is set up as shown, run the ButtonLatencyTester2.exe program
on the Windows PC host.  On the command line, you must specify the button
configuration, mapping the following elements:

* Windows event input button name

* BLT-II Pico GPIO port number

* BLT-II Pico device ID (only required if you have more than one BLT-II Pico connected)

The full structure of the button mapping looks like this:

<tt><i>button-name</i><b>:</b><i>gpio-number</i></tt>

For example, if the button is mapped on the subject device to generate
virtual "Escape" key presses on the keyboard, and the Pico connection
is to GP0, you'd enter a command line like this:

`esc:0`

If the button on the subject is mapped to joystick button #3, and it's
connected to GPIO 12 on the BLT-II Pico:

`js3:12`

For a full list of accepted button names, run the program with the `--buttons` option.

### Raw Input vs DirectInput

The Windows host program gives you the option to measure keyboard
and joystick/gamepad input through two APIs: Raw Input and DirectInput.
This is purely a choice on the Windows side, and has nothing at all to
do with the subject device, which only thinks in terms of keyboard
or joystick/gamepad input at the USB level.  If the device provides
keyboard input, you can use Raw Input or DirectInput interchangeably.

Raw Input is always selected by default.  To use DirectInput instead,
specify `--api directinput` on the command line.

The reason that the host program offers both options is that *applications*
can use either API.  Choosing the same API that your target application
uses will most accurately re-create the conditions in effect during
real sessions with the application, for accurate measurement of the
latency that you'll see in practice using that application.

The choice of APIs is also meant to be useful to application
developers to compare the latency impact of different API choices.

## End-to-end latency measurement

Other people have devised ways to measure latency in gaming devices,
so this isn't exactly a new science.  But Button Latency Tester II
brings something to the table that I think is unique among testing
methods: **end-to-end** testing.  That means that the tool measures
the latency across the complete input path, from the moment of the
physical switch contact that signifies the button press, to the moment
where the application receives the corresponding Windows input event.

Most other latency measuring methods read USB input directly from the
subject device.  That's good for comparing *relative* latencies
between devices, but it doesn't tell you the true latency, taking into
account the transit through the Windows software layers.  This is
important because Windows has a very complex input processing model
with many redundant APIs.  The overall latency is not only a function
of the latency as far as the physical input port to the PC, but also
of the class of input event (keyboard, joystick, XInput, Open Pinball
Device) *and* the specific API that the application uses to read its
input.  BLT-II lets you see the full picture, measuring the full time
from physical button press to final application input ingestion point.
This lets you optimize not just the choice of device, but also which
type of input it's sending and which APIs the application uses to
process the input.

Another capability that I think is unique is that BLT-II can be used
to measure latency with <b>non</b>-USB devices, such as devices that
connect to an RS-232 serial port input or a PS/2 keyboard.  The BLT-II
Pico doesn't have to connect directly to the subject device, so it
doesn't matter how the subject device connects to the PC.  Everything
is mediated through the host PC.  As long as an **application** can
receive input from the subject device, we're in business; it doesn't
matter what physical path through which physical ports the input took
along the way.

## Instrumenting an application

One more interesting thing you can do with BLT-II is use it to
instrument an application, to see what latencies look like in that
specific application.

BLT-II comes with its own Windows host application that's designed to
measure the input latency all the way through the Windows input API
layers.  That's an excellent basis for comparing latencies among
devices *and* among different Windows APIs, but it doesn't tell you
how any given application will experience latency.  Applications add
their own input processing layers that can add latency beyond the
point of event ingestion from the Windows APIs.

For example, if an application uses a polling model to read input, and
it only polls for input once per video refresh cycle, its mean latency
will be at least half of the video refresh cycle time, which is about
8 ms for a 60 Hz display, and its worst-case latency will be at least
one full refresh cycle, 16 ms.  In can be difficult to understand
these effects purely from analysis of an application's architecture or
inspection of its source code, because any "real" application is a
complex system, and it can exhibit behaviors that arise from
interactions among its parts that aren't obvious on inspection.  The
best way to truly understand these effects is to measure them.

BLT-II includes a C++ "library" module that's relatively easy to embed
in a C++ application.  (It could also be worked into a .Net application,
but that would take a little more work, since the interfaces for
importing native code aren't the friendliest part of .Net.  It might
be easier to "port" the library module to C#, which would let you
use it directly in any .Net language.)

The only bit of "design" work that you'll have to do to add BLT-II
instrumentation to an existing program is to decide how you're going
to map input events to BLT-II GPIO ports.  The BLT-II host program is
a bad example, because it's trying to achieve maximum generality, by
allowing the user to map essentially any type of HID input, through
multiple APIs.  That's why it has that horrendous command-line syntax
where you have to specify the API, button name, and GPIO port for
every input you want to monitor.  You *could* add the same sort of
thing in an existing program, but I don't recommend it.  Instead, I'd
recommend using a simple "fixed" mapping, where you **pre-define** the
inputs you want to monitor and how they're assigned to BLT-II Pico
GPIO ports.  You then leave it up to the user to wire the BLT-II Pico
to the ports as you specify.  This means that the user doesn't have to
provide any new configuration input to your program, and your program
doesn't have to parse any new input.

For a pinball program, for example, you could decide that you only
care about testing latency for the flipper button inputs, and that
these must be wired on the BLT-II to ports GP0 and GP1, respectively,
for the left and right flipper buttons.  You instruct the user to wire
things so that the flipper buttons are connected to the BLT-II Pico on
GP0 and GP1.  There's nothing extra the user has to specify when
running your program, and no extra code in your program to parse new
configuration files or command line options.

Once you've decided on an input mapping strategy, the rest is pretty
straightforward.  The BLT-II add-in module is self-contained, and
you only have to add a few function calls to your program to make
it work.  Here's the procedure:

* Add the files `BLTVendorInterface.h` and `BLTVendorInterface.cpp` to your project

* In your program's startup code, call `ButtonLatencyTester2::VendorInterface::EnumerateDevices()`
to get a list of "descriptors" that represent the connected BLT-II Picos.  If you want to keep
things simple, you can assume that only BLT-II Pico is ever attached at once, and fail with an error if
the list is empty or has more than one entry.

* Open live connections to the BLT-II device or devices, by calling `Open()` on the descriptors
returned from `EnumerateDevices()`.  This hands you back a "device interface" object that represents
a live USB connection to the Pico.  This is what you use to communicate with the Pico later on
to notify it when you receive input events that it's monitoring.

* At the point in your application where you read input events from the Windows API, mark the
microsecond-clock time of each event by calling `ButtonLatencyTester2::VendorInterface::GetMicrosecondTime()`.
You should record this time for each event as soon as possible after calling the input API, since
this defines the "receive" end of the latency calculation.  If your application has its own
input processing layers that must be traversed before the application will be able to interpret
and respond to the event, you should take the time reading **after** traversing those layers,
since what you're really trying to measure here is how quickly the application can **react**
to an event.  For example, if you have a low-level routine that reads input from a Windows
API, but it then places the event in an internal queue that will be processed on another
thread, you should take the time measurement when the other thread receives the event.
The time that the event spends sitting in the queue contributes to the user's perception
of the latency, so it should be included in the time calculation.

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
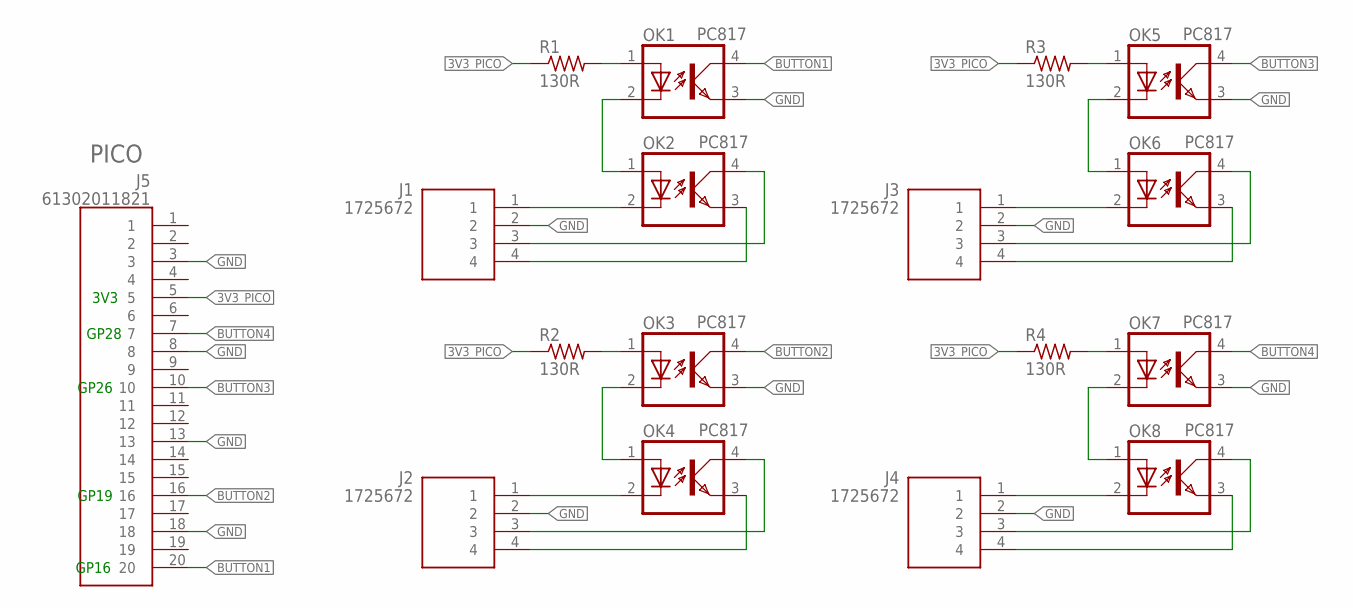
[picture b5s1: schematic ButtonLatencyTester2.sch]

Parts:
J1, J2, J3, J4: 1725672; 1725672-4-2.54
J5: 61302011821; RHDR20W60P0X254_1X20_5130X250X
OK1, OK2, OK3, OK4, OK5, OK6, OK7, OK8: PC817; DIL04
R1, R2, R3, R4: 130R; 0204/7

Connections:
3V3_PICO: J5.5, R1.1, R2.1, R3.1, R4.1
BUTTON1: J5.20, OK1.4 (COL)
BUTTON2: J5.16, OK3.4 (COL)
BUTTON3: J5.10, OK5.4 (COL)
BUTTON4: J5.7, OK7.4 (COL)
GND: J1.2, J2.2, J3.2, J4.2, J5.3, J5.8, J5.13, J5.18, OK1.3 (EMIT), OK3.3 (EMIT), OK5.3 (EMIT), OK7.3 (EMIT)
unnamed: OK1.1 (A), R1.2
unnamed: OK3.1 (A), R2.2
unnamed: OK1.2 (C), OK2.1 (A)
unnamed: J1.4, OK2.3 (EMIT)
unnamed: J1.1, OK2.2 (C)
unnamed: J1.3, OK2.4 (COL)
unnamed: OK3.2 (C), OK4.1 (A)
unnamed: J2.1, OK4.2 (C)
unnamed: J2.4, OK4.3 (EMIT)
unnamed: J2.3, OK4.4 (COL)
unnamed: OK5.1 (A), R3.2
unnamed: OK5.2 (C), OK6.1 (A)
unnamed: J3.1, OK6.2 (C)
unnamed: J3.4, OK6.3 (EMIT)
unnamed: J3.3, OK6.4 (COL)
unnamed: OK7.1 (A), R4.2
unnamed: OK7.2 (C), OK8.1 (A)
unnamed: J4.1, OK8.2 (C)
unnamed: J4.4, OK8.3 (EMIT)
unnamed: J4.3, OK8.4 (COL)

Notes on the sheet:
3V3
GP26
GP19
GP28
GP16
PICO

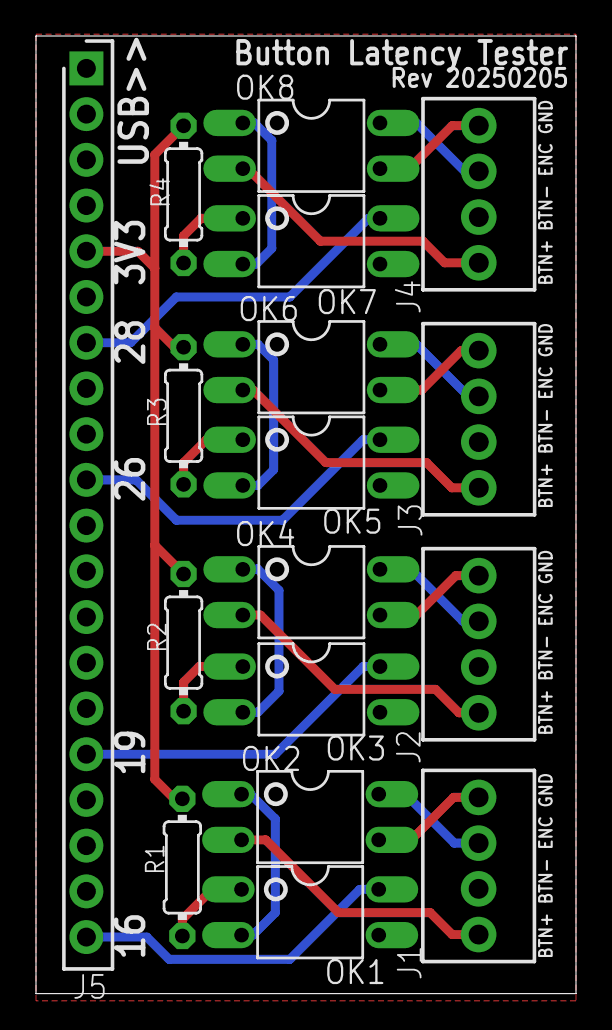
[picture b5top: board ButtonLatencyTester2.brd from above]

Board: 2 copper layers, 30.0 x 53.2 mm, 17 parts (0 on the bottom side), 26 nets.

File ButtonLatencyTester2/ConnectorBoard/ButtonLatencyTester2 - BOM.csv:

Qty,Value,Parts,Description,MOUSER_PART_NUMBER,ExtDescription
4,130R,"R1, R2, R3, R4","Resistor, 130 Ohm, axial, 2mm x 4mm",MF0204FTE52-130R,"Resistor, 130 Ohm, axial, 2mm x 4mm (R1, R2, R3, R4)"
4,1725672,"J1, J2, J3, J4","Phoenix Contact PCB terminal block, 4 way, 26-20 AWG, 2.54mm pitch",651-1725672,"Phoenix Contact PCB terminal block, 4 way, 26-20 AWG, 2.54mm pitch (J1, J2, J3, J4)"
1,61302011821,J5,"Socket Header, 20 position, 2.54mm pitch",710-61302011821,"Socket Header, 20 position, 2.54mm pitch (J5)"
8,PC817,"OK1, OK2, OK3, OK4, OK5, OK6, OK7, OK8","Optocoupler PC817 / LTV-817, DIP",PC817X2NSZ9F,"Optocoupler PC817 / LTV-817, DIP (OK1, OK2, OK3, OK4, OK5, OK6, OK7, OK8)"
